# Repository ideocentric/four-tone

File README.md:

# four-tone

A four-note organ played by computer fans. An Arduino Nano runs a sequence
through four 12 V blower fans, and each fan blows into a 3D printed,
recorder-style head joint on a length of 2" PVC pipe. All four voices are identical
except for the pipe length, which sets the note.

## How it works

```mermaid
flowchart LR
    PSU["Power supply<br/>12 V + 5 V"] --> BOARD["Six fan driver<br/>+ Arduino Nano"]
    BOARD -- "PWM, 4 channels" --> FANS["4 x 5015 blower fans"]
    FANS --> HEADS["Printed head joints"] --> PIPES["PVC pipes<br/>cut to pitch"]
```

- **Firmware:** the Nano steps through 24 phrases (every ordering of the four
  pipes, then a rest) against 5 rhythms, at 50 BPM. Each note fades its fan up
  over 250 ms and back down after. The pattern takes 14.4 minutes to repeat.
- **Driver board:** a carrier for the Nano with six MOSFET fan channels, an
  indicator LED per channel, and a screw terminal for the supply. four-tone uses
  four channels.
- **Voices:** a 5015 blower in a printed caddy, hot glued into a printed head
  joint, on a 2" PVC pipe. The head joint holds the windway, window and labium,
  like the head joint of a contrabass recorder or the mouth of an organ flue pipe.

## Status

| Part | State |
| ---- | ----- |
| Head joint and fan caddy | Printed and working; the head joint is tested with 2" PVC |
| Head joint rev 03 | Hollowed for resin printing, quoted at $32.65 landed; not yet printed |
| Enclosure | Built: an open-bottom wooden box. Dimensions not yet documented |
| Driver board | Rev A designed and ordered from JLCPCB (2026-09-15) |
| Firmware | Builds for the Nano; not yet run on the rev A board |
| Pipes | Target notes and lengths not yet chosen |
| Wooden head joint | Explored for viability: modelled, drawn and ready to quote. Not built, not chosen |

[Status and how to resume](docs/status.md) has the full picture, the open
questions and the commands to rebuild anything.

## Documentation

| Guide | For |
| ----- | --- |
| [Build guide](docs/build.md) | Assembly, wiring, and step-by-step power-up checks |
| [Tuning guide](docs/tuning.md) | Finding pipe lengths for your notes, with a calculator |
| [Print sourcing](docs/print-sourcing.md) | Where to print the head joints: quotes, tariffs and landed cost |
| [Wooden head joint](docs/wood-head-joint.md) | A wooden version, explored for viability and ready to quote |
| [Status](docs/status.md) | Where the project stands, what is open, and how to resume |
| [Firmware](firmware/README.md) | Building, uploading, how the sequence works, changing the music |
| [Driver board](hardware/pcb/README.md) | Schematic, BOM, circuit and layout notes |
| [Parts list](hardware/parts.md) | Everything to buy or make |
| [Mechanical](mechanical/README.md) | Head joint and caddy models, printing, enclosure |

## Repository layout

```
four-tone/
├── platformio.ini        Firmware build configuration
├── firmware/             Arduino firmware (PlatformIO, C++)
├── hardware/
│   ├── parts.md          Parts list
│   ├── pcb/              Six fan driver: KiCad project and fabrication files
│   ├── art/              Silkscreen logo source
│   └── datasheets/       Reference datasheets
├── mechanical/           FreeCAD models: head joint, fan caddy, wooden version
├── tools/                Tuning calculator; model and drawing generators
└── docs/                 Build and tuning guides, images
```

## License

Copyleft throughout: firmware and tools under GPL-3.0-or-later, the driver board
under CERN-OHL-S-2.0, and the mechanical design and documentation under
CC-BY-SA-4.0. See [LICENSE.md](LICENSE.md). Per-file details are in
[REUSE.toml](REUSE.toml).

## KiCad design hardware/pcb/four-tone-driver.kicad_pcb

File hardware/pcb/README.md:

# Six fan driver, rev A

An Arduino Nano carrier board with six low-side MOSFET fan channels. four-tone
uses four of them; the other two are spare for other projects. It is designed for
JLCPCB fabrication and assembly, and rev A was ordered on 2026-09-15.

| File | What it is |
| ---- | ---------- |
| `four-tone-driver.kicad_sch` | Schematic (KiCad 9). [PDF](../../docs/images/six-fan-driver-rev-a-schematic.pdf) |
| `four-tone-driver.kicad_pcb` | Board layout (KiCad 9) |
| `four-tone-driver.kicad_pro` | Project settings, including the `Power` net class |
| `fabrication/rev-a/` | Gerbers, drill files, BOM and CPL as ordered, with the export settings |

The KiCad files keep the project's original `four-tone-driver` name; the board
itself is titled "six fan driver". Every symbol carries its JLCPCB/LCSC part
number in an `LCSC` field.

## BOM

| Designators | Qty | Part | Package | LCSC | JLC type |
| ----------- | --- | ---- | ------- | ---- | -------- |
| Q1-Q6 | 6 | AO3400A N-MOSFET, 30 V 5.7 A | SOT-23 | C20917 | Basic |
| D1-D6 | 6 | SS14 Schottky flyback diode, 1 A 40 V | SMA | C2480 | Basic |
| D11-D16 | 6 | Red LED, channel indicator | 0603 | C2286 | Basic |
| R1-R6 | 6 | 1 k gate resistor | 0603 | C21190 | Basic |
| R11-R16 | 6 | 100 k gate pull-down | 0603 | C25803 | Basic |
| R21-R26 | 6 | 4.7 k LED resistor | 0603 | C23162 | Basic |
| C1 | 1 | 100 uF 25 V electrolytic, 12 V bulk | SMD 6.3 x 7.7 mm | C72477 | Extended |
| C2, C4 | 2 | 10 uF 25 V X5R, 12 V and 5 V bulk | 0805 | C15850 | Basic |
| C3, C5 | 2 | 100 nF 50 V X7R, 12 V and 5 V decoupling | 0603 | C14663 | Basic |
| J1 | 1 | 4-pin screw terminal, 5.08 mm | THT | C2915641 | Extended |
| J2, J3 | 2 | 1x15 female header, 2.54 mm (Nano socket) | THT | C7499333 | Extended |
| J11-J16 | 6 | JST B2B-XH-A, 2-pin vertical (genuine JST) | THT | C158012 | Extended |

Availability was checked on 2026-09-15 through tscircuit's jlcsearch mirror of
the JLCPCB catalogue, and every line was in stock. Stock changes, so re-check in
JLCPCB's BOM tool when ordering.

## Circuit

- **Power, J1:** pin 1 +12 V, pin 2 GND, pin 3 +5 V, pin 4 GND. The two grounds
  are joined on the board, so the supply's 5 V and 12 V returns must be common.
  Confirm this with a meter before connecting (see the
  [build guide](../../docs/build.md)).
- **Logic power:** +5 V feeds the Nano's `+5V` pin directly through the socket,
  bypassing its regulator. `VIN` is not connected. The Nano reference design has
  a Schottky diode on USB VBUS, so the supply cannot back-feed a computer while
  USB is plugged in for programming. Clones vary; check the ones you use.
- **Each fan channel:** a Nano PWM pin drives the AO3400A gate through 1 k, with
  a 100 k pull-down to GND so the fan stays off while the Nano resets or is
  unplugged. The MOSFET switches the fan's return (connector pin 2) to GND. An
  SS14 across the fan clamps the lead inductance. A red LED with 4.7 k from
  +12 V to the switched return lights when the channel is on (about 2 mA) and
  follows the PWM ramp. It lights with no fan plugged in, which helps testing.
- **Fan connectors J11-J16:** pin 1 +12 V (marked + on the silkscreen), pin 2
  switched return.
- **Current:** the fans are rated 0.18 A. The design allows 0.5 A per channel for
  start-up and 3 A for all six. The AO3400A is about 30 mOhm at 5 V gate drive,
  so it dissipates under 10 mW per channel.

## Channel to pin map

| Channel | Connector | Nano pin | PWM timer (Nano) | four-tone firmware |
| ------- | --------- | -------- | ---------------- | ------------------ |
| 1 | J11, FAN1 | D3 | Timer2, ~490 Hz | pipe 1 |
| 2 | J12, FAN2 | D5 | Timer0, ~980 Hz | pipe 2 |
| 3 | J13, FAN3 | D6 | Timer0, ~980 Hz | pipe 3 |
| 4 | J14, FAN4 | D9 | Timer1, ~490 Hz | pipe 4 |
| 5 | J15, FAN5 | D10 | Timer1, ~490 Hz | spare |
| 6 | J16, FAN6 | D11 | Timer2, ~490 Hz | spare |

Channels follow the order of the pins along the Nano's header, so the six gate
traces fan out without crossing. D13 is avoided: it has no PWM, and the
bootloader flashes its LED at every reset, which would blip a fan.

## Layout

- **Board:** 130 x 70 mm, 2 layers, 2 mm corner radius, M3 holes 4 mm in from
  each corner.
- **Edges:** fan connectors along the bottom edge, 19 mm apart, each channel's
  parts directly behind its connector. Power terminal on the left edge, wire
  entry facing out, +12 V at the top. Nano sockets along the top right with the
  USB end at the right edge.
- **Nano sockets:** J2 pin k is Nano pin k; J3 pin k is Nano pin 31-k. The
  placement was checked pad for pad against KiCad's `Module:Arduino_Nano`
  footprint.
- **Copper:** GND pours on both layers, stitched with vias. The `Power` net class
  (+12 V, +5 V, GND, FANn_DRV) uses 0.8 mm tracks with 0.25 mm clearance;
  everything else is 0.3 mm with 0.2 mm clearance.
- **Silkscreen:** board name and revision, the licence (CERN-OHL-S-2.0), and the
  source location `github.com/ideocentric/four-tone`, which CERN-OHL-S asks
  products to carry. The ensō house mark sits beside that block
  (source: [`../art/enso-oro.svg`](../art/README.md)). FAN1-FAN6 labels are on
  the board-edge side of the connectors with + beside pin 1, and an outline of
  the Nano's USB connector shows which way round the Nano goes.
- **Checks:** ERC 0 violations; DRC 0 violations, 0 unconnected, 0 schematic
  parity issues (KiCad 9.0.6).

## Known limitations of rev A

- **J1 footprint:** the layout uses KiCad's Phoenix MKDS 1.5 5.08 mm footprint for
  the DB128V-5.08-4P terminal in the BOM (C2915641). Compare the hole size and
  body outline with the real part when the boards arrive.
- **Brushless fans on PWM:** 2-wire brushless fans have their own driver inside.
  Switching their supply with PWM can make them stall or tick at low duty, and
  the ~490 Hz PWM can be audible. The firmware only ramps briefly (250 ms), but
  test one fan before relying on low duty cycles.
- **Fan lead length:** the fans used here have 11" (280 mm) leads, so the board
  has to sit within about 250 mm of each fan once slack is allowed for.

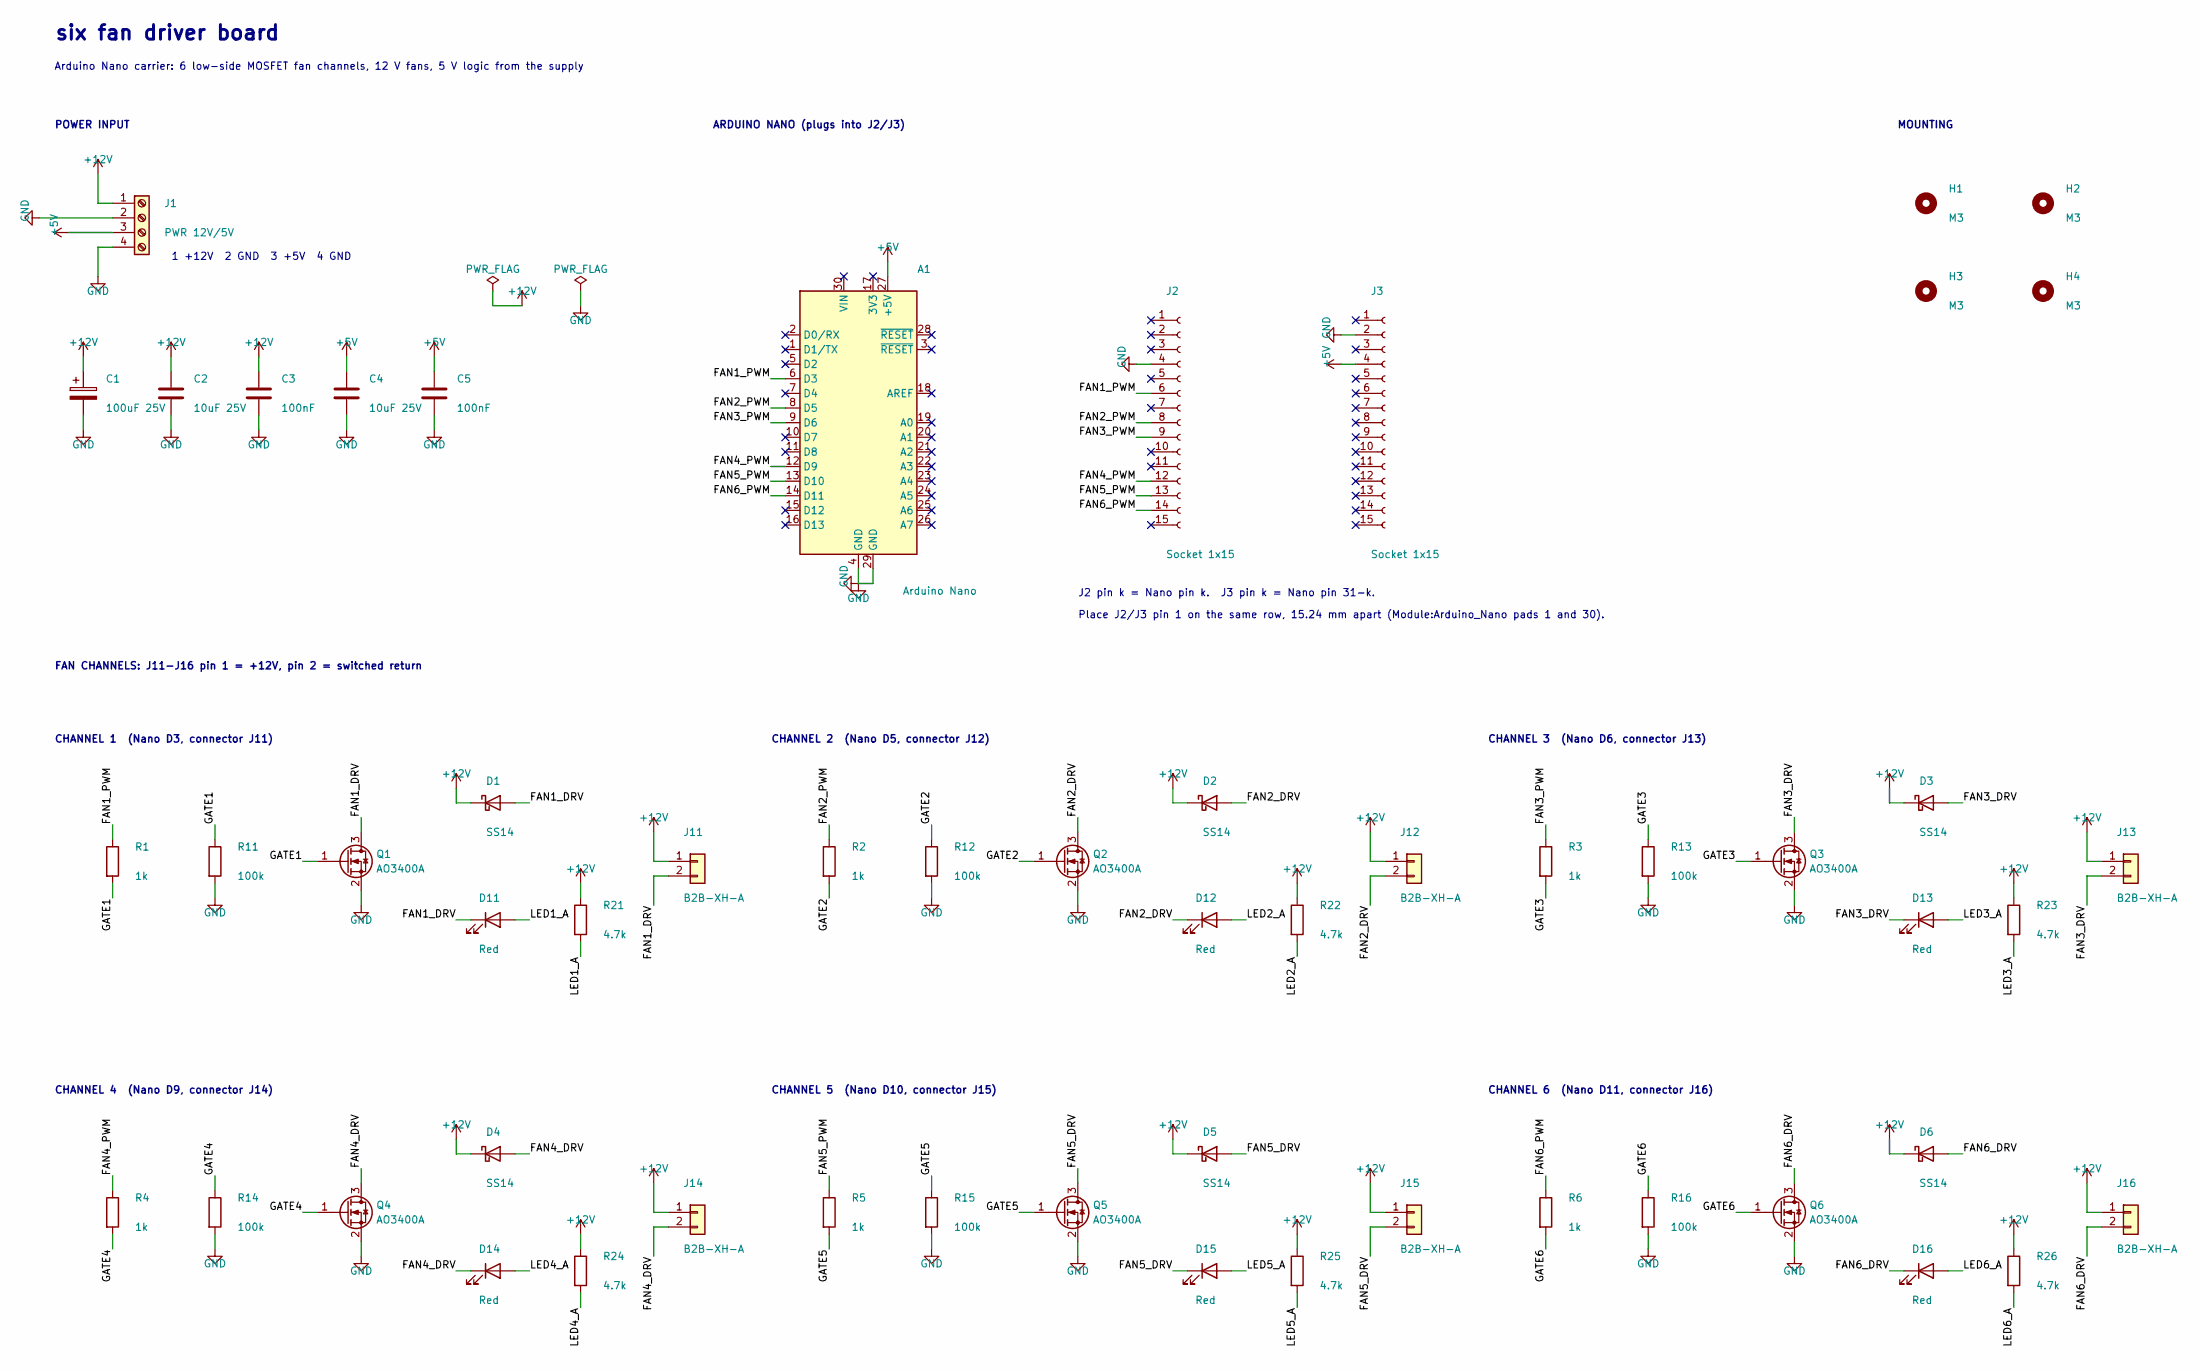
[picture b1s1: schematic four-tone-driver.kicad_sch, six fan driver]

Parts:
A1: Arduino Nano
C1: 100uF 25V; CP_Elec_6.3x7.7; LCSC C72477
C2, C4: 10uF 25V; C_0805_2012Metric; LCSC C15850
C3, C5: 100nF; C_0603_1608Metric; LCSC C14663
D1, D2, D3, D4, D5, D6: SS14; D_SMA; LCSC C2480
D11, D12, D13, D14, D15, D16: Red; LED_0603_1608Metric; LCSC C2286
H1, H2, H3, H4: M3; MountingHole_3.2mm_M3
J1: PWR 12V/5V; TerminalBlock_Phoenix_MKDS-1,5-4-5.08_1x04_P5.08mm_Horizont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; LCSC C2915641
J2, J3: Socket 1x15; PinSocket_1x15_P2.54mm_Vertical; LCSC C7499333
J11, J12, J13, J14, J15, J16: B2B-XH-A; JST_XH_B2B-XH-A_1x02_P2.50mm_Vertical; LCSC C158012
Q1, Q2, Q3, Q4, Q5, Q6: AO3400A; SOT-23; LCSC C20917
R1, R2, R3, R4, R5, R6: 1k; R_0603_1608Metric; LCSC C21190
R11, R12, R13, R14, R15, R16: 100k; R_0603_1608Metric; LCSC C25803
R21, R22, R23, R24, R25, R26: 4.7k; R_0603_1608Metric; LCSC C23162

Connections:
+5V: A1.27 (+5V), C4.1, C5.1, J1.3, J3.4
+12V: C1.1, C2.1, C3.1, D1.1 (K), D2.1 (K), D3.1 (K), D4.1 (K), D5.1 (K), D6.1 (K), J1.1, J11.1, J12.1, J13.1, J14.1, J15.1, J16.1, R21.1, R22.1, R23.1, R24.1, R25.1, R26.1
/FAN1_DRV: D1.2 (A), D11.1 (K), J11.2, Q1.3 (D)
/FAN1_PWM: A1.6 (D3), J2.6, R1.1
/FAN2_DRV: D2.2 (A), D12.1 (K), J12.2, Q2.3 (D)
/FAN2_PWM: A1.8 (D5), J2.8, R2.1
/FAN3_DRV: D3.2 (A), D13.1 (K), J13.2, Q3.3 (D)
/FAN3_PWM: A1.9 (D6), J2.9, R3.1
/FAN4_DRV: D4.2 (A), D14.1 (K), J14.2, Q4.3 (D)
/FAN4_PWM: A1.12 (D9), J2.12, R4.1
/FAN5_DRV: D5.2 (A), D15.1 (K), J15.2, Q5.3 (D)
/FAN5_PWM: A1.13 (D10), J2.13, R5.1
/FAN6_DRV: D6.2 (A), D16.1 (K), J16.2, Q6.3 (D)
/FAN6_PWM: A1.14 (D11), J2.14, R6.1
/GATE1: Q1.1 (G), R1.2, R11.1
/GATE2: Q2.1 (G), R2.2, R12.1
/GATE3: Q3.1 (G), R3.2, R13.1
/GATE4: Q4.1 (G), R4.2, R14.1
/GATE5: Q5.1 (G), R5.2, R15.1
/GATE6: Q6.1 (G), R6.2, R16.1
/LED1_A: D11.2 (A), R21.2
/LED2_A: D12.2 (A), R22.2
/LED3_A: D13.2 (A), R23.2
/LED4_A: D14.2 (A), R24.2
/LED5_A: D15.2 (A), R25.2
/LED6_A: D16.2 (A), R26.2
GND: A1.4 (GND), A1.29 (GND), C1.2, C2.2, C3.2, C4.2, C5.2, J1.2, J1.4, J2.4, J3.2, Q1.2 (S), Q2.2 (S), Q3.2 (S), Q4.2 (S), Q5.2 (S), Q6.2 (S), R11.2, R12.2, R13.2, R14.2, R15.2, R16.2

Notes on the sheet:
six fan driver board
Arduino Nano carrier: 6 low-side MOSFET fan channels, 12 V fans, 5 V logic from the supply
POWER INPUT
1 +12V 2 GND 3 +5V 4 GND
ARDUINO NANO (plugs into J2/J3)
J2 pin k = Nano pin k. J3 pin k = Nano pin 31-k.
Place J2/J3 pin 1 on the same row, 15.24 mm apart (Module:Arduino_Nano pads 1 and 30).
FAN CHANNELS: J11-J16 pin 1 = +12V, pin 2 = switched return
CHANNEL 1 (Nano D3, connector J11)
CHANNEL 2 (Nano D5, connector J12)
CHANNEL 3 (Nano D6, connector J13)
CHANNEL 4 (Nano D9, connector J14)
CHANNEL 5 (Nano D10, connector J15)
CHANNEL 6 (Nano D11, connector J16)
MOUNTING

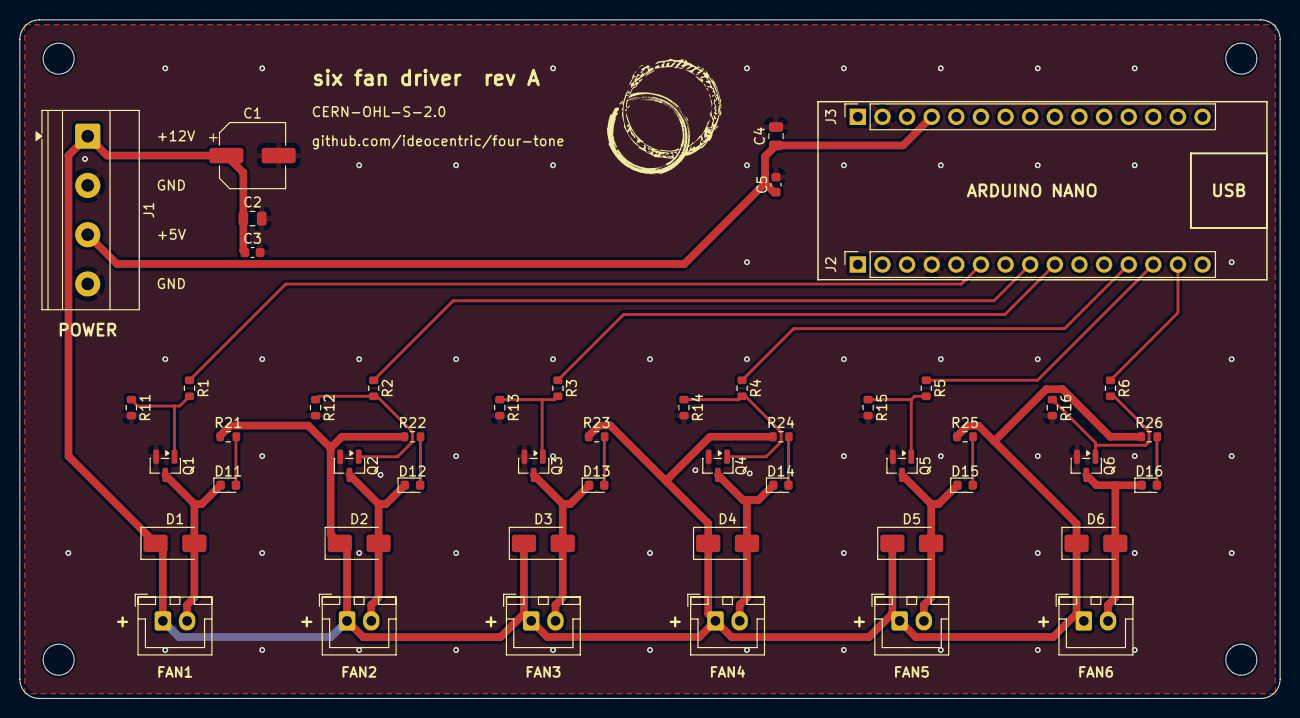
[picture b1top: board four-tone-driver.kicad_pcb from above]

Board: 2 copper layers, 130.0 x 70.0 mm, 54 parts (0 on the bottom side), 27 nets.

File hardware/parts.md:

# Parts

## Purchased

| Qty | Part | Specs | Source |
| --- | ---- | ----- | ------ |
| 4 | UMLIFE 5015 blower fan, 12 V version | Label `DF5015FAN DC12V 0.18A`. 50 x 50 x 15 mm, 19.5 mm outlet, 5700 RPM, 25 dBA, oil bearing. 2-pin plug, pitch measured 2.54 mm (JST XH style; the listing says "PH2.5"). Lead 11" (280 mm). | [Amazon B083HQGJBR](https://www.amazon.com/dp/B083HQGJBR); dimensioned drawings are in the listing's images |
| 1 | Arcity arcade switching power supply | Outputs +5 V/8 A, +12 V/7 A, +24 V/5 A. Input 110/220 V switchable. OVP, OCP, SCP, OTP. 160 x 98 x 38 mm. | [Amazon B07RT54H9V](https://www.amazon.com/dp/B07RT54H9V) (specs from the listing, not yet checked against the unit's label) |
| 1 | Arduino Nano, classic (A000005, ATmega328P) | 16 MHz, 5 V logic, 32 KB flash, 2 KB SRAM, 6 PWM pins (D3, D5, D6, D9, D10, D11), Mini-B USB. PlatformIO env `nano` (new bootloader) or `nano_old`. | [Arduino Store](https://store-usa.arduino.cc/collections/nano-family/product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 |

A Nano Every (ABX00033, ATmega4809, [Amazon B07WWK29XF](https://www.amazon.com/dp/B07WWK29XF))
was also bought but is not the target board. It has 5 PWM pins, not the 6 the
listing claims (D3, D5, D6, D9, D10 per Arduino's datasheet and megaAVR core).
The firmware compiles for it and the fan pins are PWM on it too, so it can
stand in, but it needs `platform = atmelmegaavr`, `board = nano_every`.

The 24 V output is unused.

## Fabricated

| Qty | Part | Source |
| --- | ---- | ------ |
| 4 | Beak | `../mechanical/cad/fan_organ_pipe_rev_02.FCStd` |
| 4 | Fan caddy | `../mechanical/cad/fan_mount_rev-01.FCStd` |
| 4 | 2" PVC pipe, cut to pitch | Same stock for all four; length TBD per note |
| 1 | Open-bottom wooden enclosure | `../mechanical/enclosure/` |
| 1 | Six fan driver PCB, rev A | `pcb/four-tone-driver.kicad_pcb` (schematic and routed layout done, fabrication files not yet generated) |

## Six fan driver, rev A

Arduino Nano carrier with six low-side MOSFET fan channels (four used by this
project, two spare). Intended for JLCPCB fabrication and assembly. LCSC part
numbers are in each symbol's `LCSC` field.

### BOM

| Designators | Qty | Part | Package | LCSC | JLC type |
| ----------- | --- | ---- | ------- | ---- | -------- |
| Q1-Q6 | 6 | AO3400A N-MOSFET, 30 V 5.7 A | SOT-23 | C20917 | Basic |
| D1-D6 | 6 | SS14 Schottky flyback diode, 1 A 40 V | SMA | C2480 | Basic |
| D11-D16 | 6 | Red LED, channel indicator | 0603 | C2286 | Basic |
| R1-R6 | 6 | 1 k gate resistor | 0603 | C21190 | Basic |
| R11-R16 | 6 | 100 k gate pull-down | 0603 | C25803 | Basic |
| R21-R26 | 6 | 4.7 k LED resistor | 0603 | C23162 | Basic |
| C1 | 1 | 100 uF 25 V electrolytic, 12 V bulk | SMD 6.3 x 7.7 mm | C72477 | Extended |
| C2, C4 | 2 | 10 uF 25 V X5R, 12 V and 5 V bulk | 0805 | C15850 | Basic |
| C3, C5 | 2 | 100 nF 50 V X7R, 12 V and 5 V decoupling | 0603 | C14663 | Basic |
| J1 | 1 | 4-pin screw terminal, 5.08 mm | THT | C2915641 | Extended |
| J2, J3 | 2 | 1x15 female header, 2.54 mm (Nano socket) | THT | C7499333 | Extended |
| J11-J16 | 6 | JST B2B-XH-A, 2-pin vertical (genuine JST) | THT | C158012 | Extended |

Availability checked 2026-09-15 through tscircuit's jlcsearch mirror of the
JLCPCB catalogue; every line was in stock. Re-check in JLCPCB's BOM tool when
ordering.

### Circuit

- **Power, J1:** pin 1 +12 V, pin 2 GND, pin 3 +5 V, pin 4 GND, from the
  supply's 12 V and 5 V outputs. The two grounds are joined on the board, so
  the supply's 5 V and 12 V returns must be common. Confirm with a meter.
- **Logic power:** +5 V feeds the Nano's `+5V` pin through J3 pin 4, bypassing
  its regulator. `VIN` is left unconnected. The Nano reference design has a
  Schottky diode on USB VBUS, so the supply cannot back-feed a computer during
  programming. Clones vary; check the boards actually used.
- **Fan channel n:** Nano PWM pin, 1 k to the AO3400A gate, 100 k gate
  pull-down to GND so the fan stays off while the Nano resets or is removed.
  The MOSFET switches the fan's return (connector pin 2) to GND. An SS14 across the
  fan clamps the lead inductance. A red LED with 4.7 k from +12 V to the
  switched return lights when the channel is on (about 2 mA), and follows the
  PWM ramp. It also lights with no fan plugged in, which helps bench testing.
- **Fan connectors J11-J16:** pin 1 +12 V (marked + on the silkscreen), pin 2
  switched return. Check which pin the red lead lands on in the fan's plug
  before wiring.
- **Current:** fans are rated 0.18 A. Design margin is 0.5 A per channel for
  start-up, 3 A for all six. AO3400A at 5 V gate drive is about 30 mOhm, so
  under 10 mW per channel.

### Channel to pin map

| Channel | Connector | Nano pin | PWM timer (Nano) | Firmware |
| ------- | --------- | -------- | ---------------- | -------- |
| 1 | J11 | D3 | Timer2, ~490 Hz | pipe 1 |
| 2 | J12 | D5 | Timer0, ~980 Hz | pipe 2 |
| 3 | J13 | D6 | Timer0, ~980 Hz | pipe 3 |
| 4 | J14 | D9 | Timer1, ~490 Hz | pipe 4 |
| 5 | J15 | D10 | Timer1, ~490 Hz | spare |
| 6 | J16 | D11 | Timer2, ~490 Hz | spare |

Channels follow the order of the pins along the Nano's header, so the six gate
traces fan out without crossing. The firmware pin list
(`firmware/include/sequence.h`) is `{3, 5, 6, 9}` for pipes 1-4.

D13 is avoided: no PWM, and the bootloader flashes its LED at every reset,
which would blip a fan.

### Layout (rev A)

- **Board:** 130 x 70 mm, 2 layers, 2 mm corner radius, M3 holes 4 mm in from
  each corner.
- **Edges:** fan connectors J11-J16 in a row along the bottom edge, 19 mm
  apart, each channel's parts directly behind its connector; power terminal J1
  on the left edge with its wire entry facing out (+12 V at the top); Nano
  sockets along the top right with the USB end at the right edge, marked
  `USB >`. Power input and Nano sit directly above the channel row.
- **Silkscreen:** "six fan driver rev A", the licence (CERN-OHL-S-2.0) and the
  source location `github.com/ideocentric/four-tone`, which CERN-OHL-S asks
  products to carry. The ensō house mark, 12 mm, sits right of that block
  (source: `art/enso-oro.svg`). FAN1-FAN6 labels are on the board
  edge side of each JST header, with + beside pin 1. The Nano outline carries
  an outline of its USB connector, labelled USB, at the right-hand end between
  the socket rows, showing which way round the Nano is seated.
- **Nano sockets:** J2 pin k is Nano pin k; J3 pin k is Nano pin 31-k. The
  placement was checked pad for pad against KiCad's `Module:Arduino_Nano`
  footprint.
- **Copper:** GND pours on both layers, stitched with vias. Net class `Power`
  (+12 V, +5 V, GND, FANn_DRV) uses 0.8 mm tracks with 0.25 mm clearance;
  everything else 0.3 mm with 0.2 mm clearance.
- **Checks:** ERC 0 violations; DRC 0 violations, 0 unconnected, 0 schematic
  parity issues (KiCad 9.0.6).
- **J1 footprint:** KiCad's Phoenix MKDS 1.5 5.08 mm footprint. Check its hole
  size and body outline against the LCSC datasheet for C2915641 before
  ordering.
- **Fan leads are 11"**, so the board has to sit within about 250 mm of each
  fan once the plug and some slack are allowed for.
- **Before ordering:** JLCPCB's placement preview often shows SOT-23, SMA,
  LED and electrolytic footprints rotated relative to KiCad. Check every
  part's orientation (diode and LED cathode, capacitor polarity) in their
  preview and correct the rotation there.

### PWM behaviour

The firmware ramps each fan over 250 ms with `analogWrite()`. Breadboard-test
one fan first: 2-wire brushless fans can stall or tick at low duty, and the
~490 Hz PWM is audible.
